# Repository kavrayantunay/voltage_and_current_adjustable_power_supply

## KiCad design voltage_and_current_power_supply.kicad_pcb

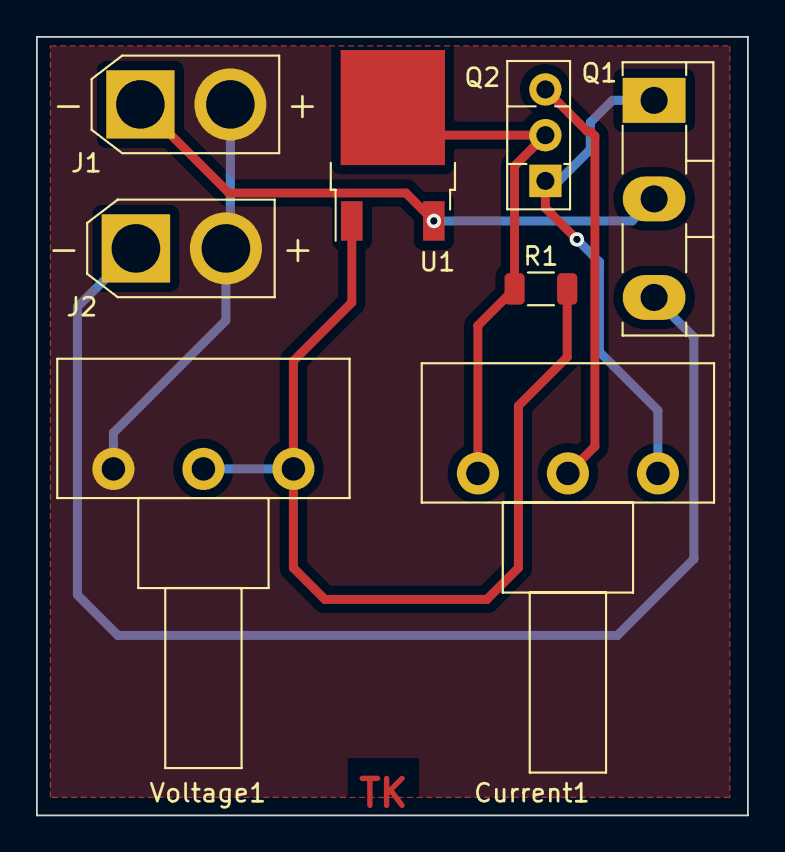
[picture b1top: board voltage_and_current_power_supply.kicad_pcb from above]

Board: 2 copper layers, 39.5 x 43.2 mm, 8 parts (0 on the bottom side), 7 nets.

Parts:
Current1: 10K; Potentiometer_Piher_T-16H_Single_Horizontal
J1, J2: Conn_01x02_Female; AMASS_XT30U-F_1x02_P5.0mm_Vertical
Q1: TIP3055; TO-218-3_Vertical
Q2: BD139; TO-126-3_Vertical
R1: 220R; R_1206_3216Metric
U1: LM317_TO-252; TO-252-2
Voltage1: 5K; Potentiometer_Piher_T-16H_Single_Horizontal

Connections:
GND: J1.2, J2.2, Voltage1.1
unnamed: Current1.1, Q2.2 (C), R1.1, U1.2 (VO)
unnamed: Current1.2, Q2.3 (B)
unnamed: Current1.3, Q1.1 (B), Q2.1 (E)
unnamed: J1.1, Q1.2 (C), U1.3 (VI)
unnamed: J2.1, Q1.3 (E)
unnamed: R1.2, U1.1 (ADJ), Voltage1.2, Voltage1.3
